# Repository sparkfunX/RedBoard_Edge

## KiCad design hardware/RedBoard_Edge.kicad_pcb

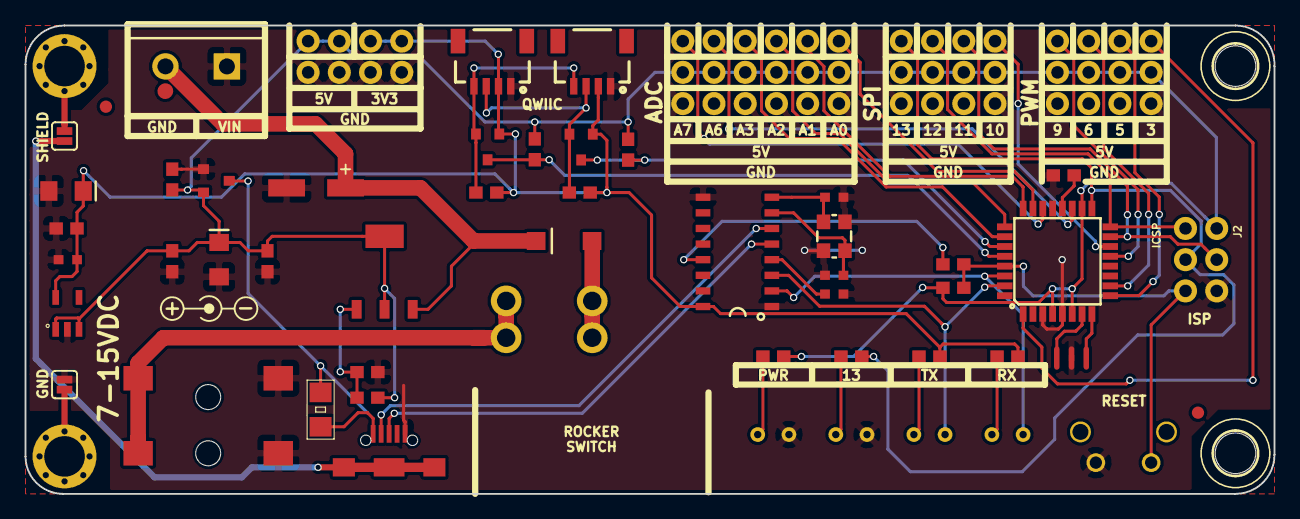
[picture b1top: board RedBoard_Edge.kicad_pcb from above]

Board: 2 copper layers, 101.6 x 38.1 mm, 66 parts (0 on the bottom side), 46 nets.

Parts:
5V1: CONN_06SILK_FEMALE_PTH; 1X06
5V2, 5V3: CONN_04; 1X04
ADC1: CONN_06SILK_FEMALE_PTH; 1X06
C1, C2, C4, C8: 0.1uF; SPARKFUN-CAPACITORS_0603
C3, C6: 10uF; SPARKFUN-CAPACITORS_EIA3216
C5: 47uF; SPARKFUN-CAPACITORS_PANASONIC_D
C7: 1.0uF; SPARKFUN-CAPACITORS_0603
C9, C10: 10pF; C_0603
C11: 10nF; C_0603
C12: 0.1uF; C_0603
D1: MBRA140; SPARKFUN-DISCRETESEMI_SMA-DIODE
D2: Green; LED_RED_T1-.75_RT_ANG_PCB
D3: Yellow; LED_RED_T1-.75_RT_ANG_PCB
D4: Red; LED_RED_T1-.75_RT_ANG_PCB
D5: Blue; LED_RED_T1-.75_RT_ANG_PCB
F1: SPARKFUN-FUSES_PTC-HALF_AMP; SPARKFUN-FUSES_1206
GND1: CONN_06SILK_FEMALE_PTH; 1X06
GND2, GND3: CONN_04; 1X04
IC3: LM1117; TESTING_SOT223-ALT1
J1: CONN_025MM; SCREWTERMINAL-5MM-2
J2: ICSP; 2X3-NS
J3: POWER_JACKSUPER_BOMB_DIGITY; TESTING_POWER_JACK_SMD_OVERPASTE_SUPER_BOMB_DIGITY
J4: microB; USB-B-MICRO-SMD
J5, J6: CONN_04; 1X04
J17, J18: Qwiic_Connector; SparkX-1X04_1MM_RA
JP1, JP2: JUMPER-SMT_2_NO_SILK; SMT-JUMPER_2_NO_SILK
JP4, JP6: STAND-OFF; SPARKFUN_STAND-OFF
JP8, JP9: FIDUCIAL1X2; SPARKFUN_FIDUCIAL-1X2
PWM1: CONN_04; 1X04
Q1: 1A/60V/500mO; SPARKFUN-DISCRETESEMI_SOT23-3
Q2, Q3: MOSFET-NCH-BSS138; SparkFun-DiscreteSemi-SOT23-3
R1, R2, R5, R6: 1k; SPARKFUN-RESISTORS_0603
R3, R4: 10k; SPARKFUN-RESISTORS_0603
R7, R8, R9, R10: 4.7k; SPARKFUN-RESISTORS_0603
R14: 715; SPARKFUN-RESISTORS_0603
R15: 240; SPARKFUN-RESISTORS_0603
S1: RESET; SWITCH_TACTILE_SPST-NO_0.05A_12V
S2: SWITCH-SPDT-PTH-11.6X4.0MM; RockerSwitch_RA
SPI1: CONN_04; 1X04
U1: CH340G; SO16
U2: MIC5205; SPARKFUN-POWERIC_SOT23-5
U3, U5: Standoff_Grounding
U4: ATMEGA328P_TQFP; SPARKFUN-IC-MICROCONTROLLER_TQFP32-08
Y1: 16MHz; SPARKFUN-CLOCKS_RESONATOR-SMD-3.2X1.3
Y2: 12MHz; CRYSTAL-SMD-3.2X2.5MM

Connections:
3.3V: C6.+, C7.1, C12.1, J5.1, J5.2, J17.2, J18.2, Q2.1, Q3.1, R5.2, R6.1, R7.2, R8.2, U1.16, U2.5
5V: 5V1.1, 5V1.2, 5V1.3, 5V1.4, 5V1.5, 5V1.6, 5V2.1, 5V2.2, 5V2.3, 5V2.4, 5V3.1, 5V3.2, 5V3.3, 5V3.4, C2.2, C3.+, C4.1, IC3.2, IC3.4, J2.2, J5.3, J5.4, Q1.2, R2.2, R3.2, R4.2, R9.2, R10.2, R15.2, U2.1, U2.3, U4.4, U4.6, U4.18
/AD0: ADC1.6, U4.23
/AD1: ADC1.5, U4.24
/AD2: ADC1.4, U4.25
/AD3: ADC1.3, U4.26
/AD6: ADC1.2, U4.19
/AD7: ADC1.1, U4.22
/AREF: C1.1, U4.20
/DTR: C8.1, U1.13
/HI_SCL: Q2.3, R9.1, U4.28
/HI_SDA: Q3.3, R10.1, U4.27
/MISO: J2.1, SPI1.2, U4.16
/MOSI: J2.4, SPI1.3, U4.15
/PWM3: PWM1.4, U4.1
/PWM5: PWM1.3, U4.9
/PWM6: PWM1.2, U4.10
/PWM9: PWM1.1, U4.13
/RESET: C8.2, J2.5, R3.1, S1.3, U4.29
/RXI: D2.1, U1.2, U4.30
/SCK: J2.3, R1.1, SPI1.1, U4.17
/SCL: J17.4, J18.4, Q2.2, R7.1
/SDA: J17.3, J18.3, Q3.2, R8.1
/SS: SPI1.4, U4.14
/TXO: D3.1, U1.3, U4.31
/USBVCC: F1.1, Q1.3
/usb_shield: J4.SHIE, JP1.2
GND: C1.2, C2.1, C3.-, C4.2, C5.-, C6.-, C7.2, C9.2, C10.2, C11.2, C12.2, D4.1, D5.1, GND1.1, GND1.2, GND1.3, GND1.4, GND1.5, GND1.6, GND2.1, GND2.2, GND2.3, GND2.4, GND3.1, GND3.2, GND3.3, GND3.4, J1.1, J2.6, J3.GND, J4.GND, J6.1, J6.2, J6.3, J6.4, J17.1, J18.1, JP2.2, Q1.1, R14.1, S1.1, U1.1, U1.9, U2.2, U4.3, U4.5, U4.21, Y1.2, Y2.2, Y2.4
unnamed: C9.1, U1.7, Y2.3
unnamed: C10.1, U1.8, Y2.1
unnamed: C11.1, U1.4
unnamed: D1.A, S2.1
unnamed: D2.2, R5.1
unnamed: D3.2, R6.2
unnamed: D4.2, R2.1
unnamed: D5.2, R1.2
unnamed: F1.2, J4.VBUS
unnamed: IC3.1, R14.2, R15.1
unnamed: J3.VIN0, S2.2
unnamed: J4.D+, U1.5
unnamed: J4.D-, U1.6
unnamed: JP1.1, U3.1
unnamed: JP2.1, U5.1
unnamed: U4.7, Y1.1
unnamed: U4.8, Y1.3
VIN: C5.+, D1.C, IC3.3, J1.2

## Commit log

2017-08-03 Finalized Layout and ordered first run
2017-09-03 Fixed VIN Silk
